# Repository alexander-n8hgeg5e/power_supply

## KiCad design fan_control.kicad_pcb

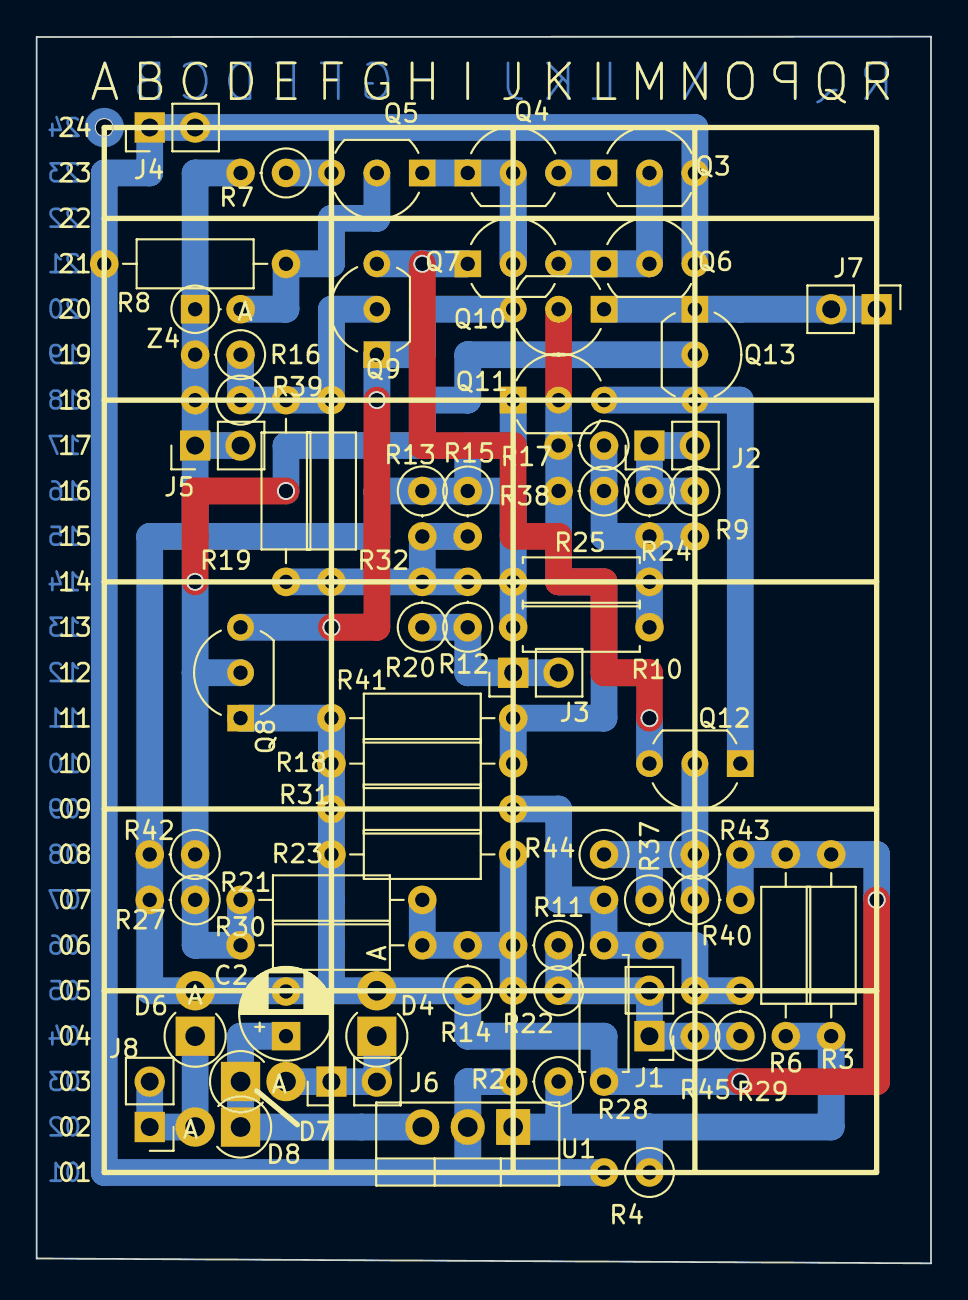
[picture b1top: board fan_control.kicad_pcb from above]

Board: 2 copper layers, 50.0 x 68.6 mm, 64 parts (0 on the bottom side), 26 nets.

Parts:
C2: elko; CP_Radial_D5.0mm_P2.50mm
D4, D6, D7, D8: 1N4007; D_DO-41_SOD81_P2.54mm_Vertical_AnodeUp
J1, J2, J3, J4, J5, J6, J7, J8: Conn_01x02_Male; PinHeader_1x02_P2.54mm_Vertical
Q3, Q4, Q6, Q7, Q8, Q9, Q10, Q11, Q12, Q13: BC557; TO-92_Inline_Wide
Q5: BC547B; TO-92_Inline_Wide
R2, R4: R; R_Axial_DIN0207_L6.3mm_D2.5mm_P2.54mm_Vertical
R3, R6: R; R_Axial_DIN0207_L6.3mm_D2.5mm_P10.16mm_Horizontal
R7: 20k; R_Axial_DIN0207_L6.3mm_D2.5mm_P2.54mm_Vertical
R8: spice; R_Axial_DIN0207_L6.3mm_D2.5mm_P10.16mm_Horizontal
R9, R24: 300K; R_Axial_DIN0207_L6.3mm_D2.5mm_P2.54mm_Vertical
R10, R25: 100K; R_Axial_DIN0207_L6.3mm_D2.5mm_P7.62mm_Horizontal
R11, R22, R29, R45: 150K; R_Axial_DIN0207_L6.3mm_D2.5mm_P2.54mm_Vertical
R12, R20: 150k; R_Axial_DIN0207_L6.3mm_D2.5mm_P2.54mm_Vertical
R13, R15: 50k; R_Axial_DIN0207_L6.3mm_D2.5mm_P2.54mm_Vertical
R14: 50K; R_Axial_DIN0207_L6.3mm_D2.5mm_P2.54mm_Vertical
R16, R17, R27, R37, R38, R39, R40, R42, R43, R44: 100K; R_Axial_DIN0207_L6.3mm_D2.5mm_P2.54mm_Vertical
R18, R19, R21, R30, R32, R41: 100K; R_Axial_DIN0207_L6.3mm_D2.5mm_P10.16mm_Horizontal
R23, R31: 50K; R_Axial_DIN0207_L6.3mm_D2.5mm_P10.16mm_Horizontal
R28: 50K; R_Axial_DIN0207_L6.3mm_D2.5mm_P7.62mm_Horizontal
U1: LM317_3PinPackage; TO-220-3_Vertical
Z4: 5V; D_DO-35_SOD27_P2.54mm_Vertical_AnodeUp

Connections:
0: C2.2, D4.2, D6.2, J5.1, J5.2, Q8.1, Q11.1, R3.2, R6.2, R7.2, R10.1, R13.1, R14.1, R15.1, R16.2, R18.2, R23.1, R25.1, R27.2, R28.2, R31.2, R39.2, R40.2, R41.2, R42.2, R43.2, Z4.1
0VAC: D6.1, D8.2, J8.1, J8.2
+15V: J4.1, J4.2, Q3.3, Q6.3, R2.2, R4.2, R8.1, U1.2
+15VAC: D4.1, D7.2, J6.1, J6.2
B: J2.1, J2.2, R9.1, R24.1
C: J3.1, J3.2, R12.1, R20.1
E: J1.1, J1.2, R11.1, R22.1, R29.1, R45.1
F+: J7.1, J7.2, Q10.1, Q13.1
unnamed: C2.1, D7.1, D8.1, U1.3
unnamed: Q3.1, Q4.3
unnamed: Q3.2, Q6.1, Q6.2, Q7.3
unnamed: Q4.1, Q4.2, Q5.1, Q7.2
unnamed: Q5.2, R8.2, Z4.2
unnamed: Q5.3, R7.1
unnamed: Q8.3, Q9.1, Q10.3
unnamed: Q11.3, Q12.1, Q13.3
unnamed: Q7.1, Q9.3, Q12.3
unnamed: R2.1, R3.1, R4.1, R6.1, U1.1
unnamed: R9.2, R10.2, R17.1, R24.2, R25.2, R38.1
unnamed: R11.2, R14.2, R21.2, R22.2, R23.2, R30.2
unnamed: R12.2, R13.2, R15.2, R19.1, R20.2, R32.1
unnamed: R28.1, R29.2, R31.1, R37.2, R44.2, R45.2
bias_i: Q10.2, Q11.2, R17.2, R18.1, R38.2, R41.1
bias_l: Q9.2, R16.1, R19.2, R32.2, R39.1
bias_o: Q8.2, Q13.2, R21.1, R27.1, R30.1, R42.1
bias_r: Q12.2, R37.1, R40.1, R43.1, R44.1

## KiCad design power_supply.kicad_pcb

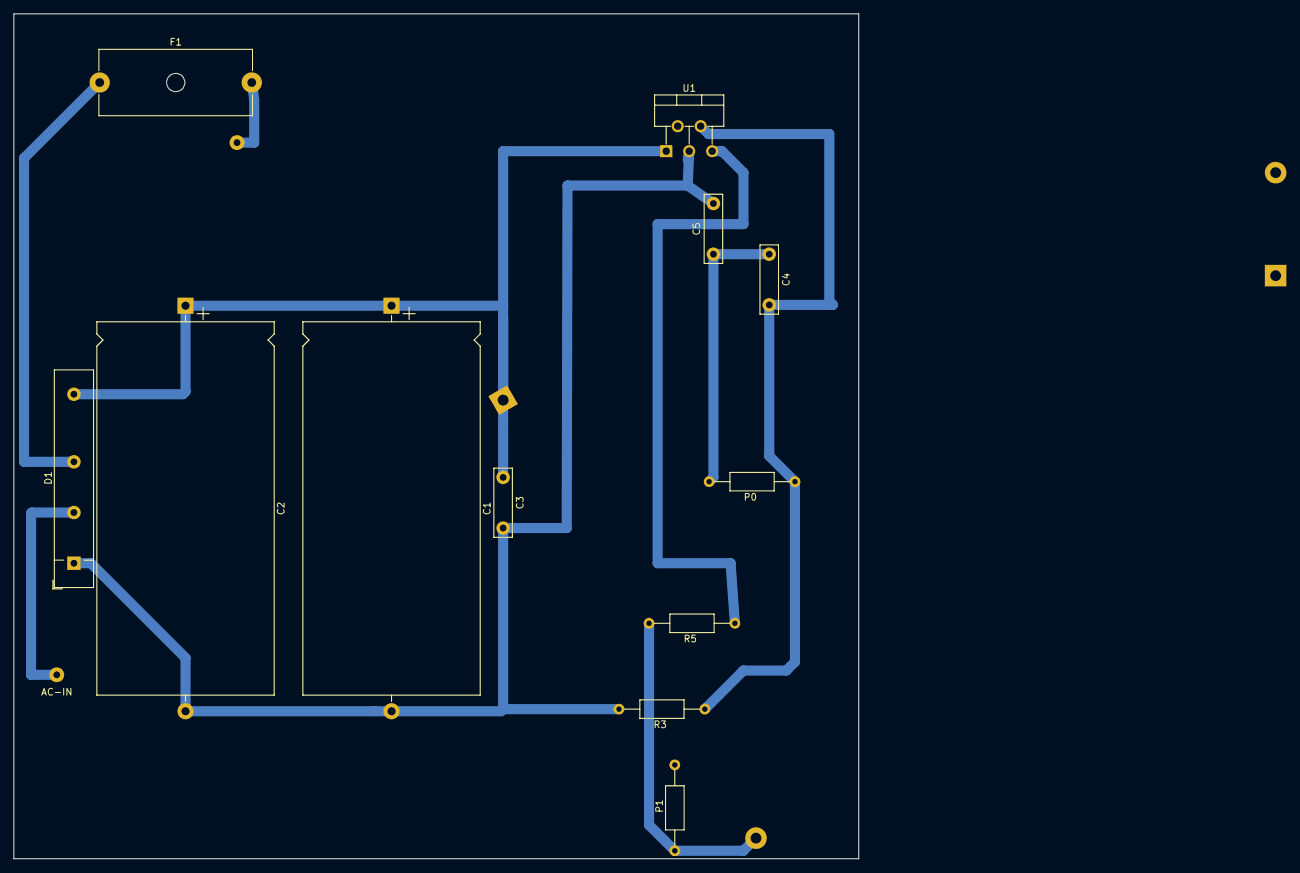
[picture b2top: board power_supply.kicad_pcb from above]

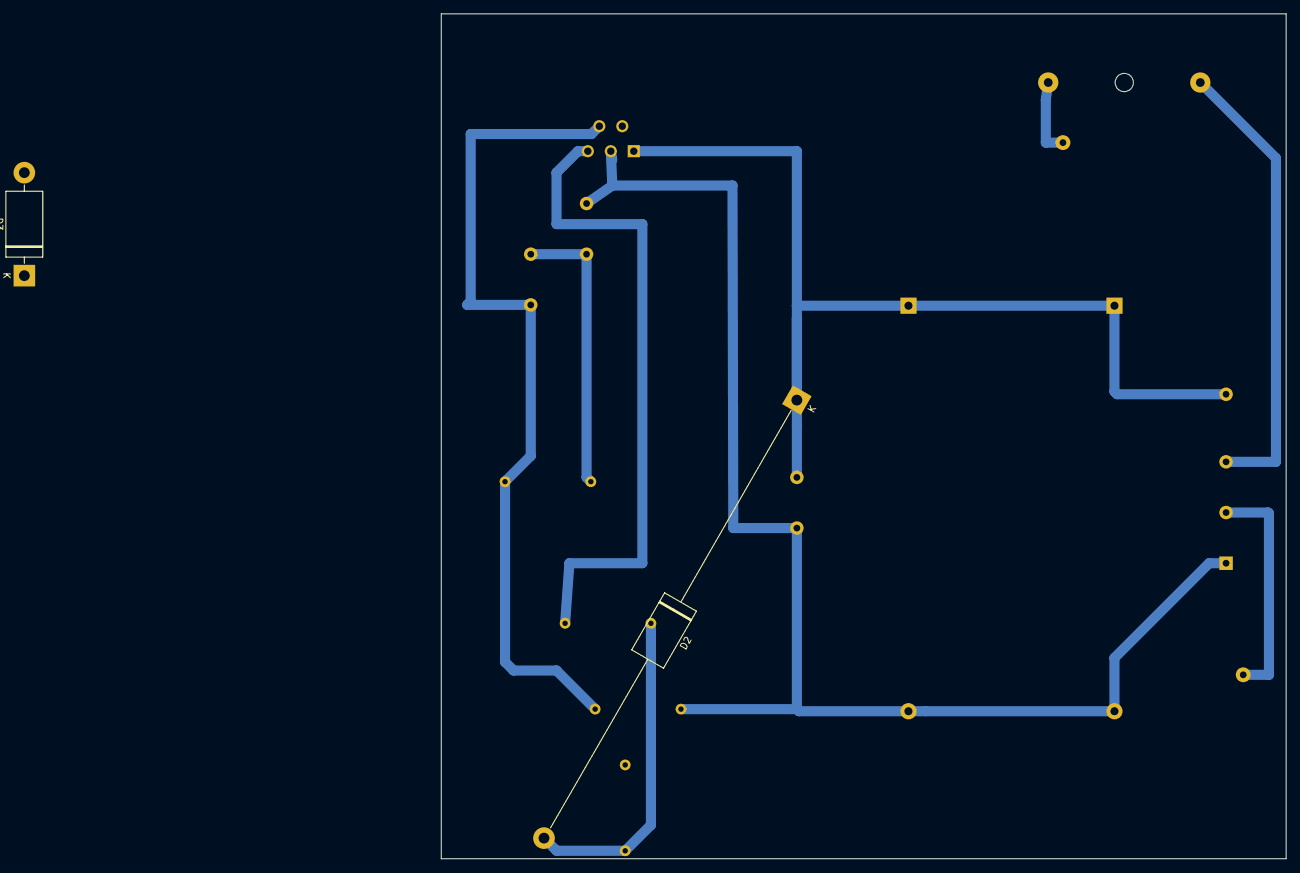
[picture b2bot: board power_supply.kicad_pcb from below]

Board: 2 copper layers, 125.0 x 125.0 mm, 14 parts (2 on the bottom side), 7 nets.

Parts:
C1: 4.7uF 63V; CP_Axial_L55.0mm_D26.0mm_P60.00mm_Horizontal
C2: 4.7mF 63V; CP_Axial_L55.0mm_D26.0mm_P60.00mm_Horizontal
C3, C4, C5: 0.1uF 100V; C_Rect_L10.0mm_W2.5mm_P7.50mm_MKS4
D1: B80C3700-2200A; Diode_Bridge_32.0x5.6x17.0mm_P10.0mm_P7.5mm
D2: 1N5408; D_DO-201AD_P75.21mm_Horizontal_extra_long
D3: 1N5408; D_DO-201AD_P15.24mm_Horizontal
F1: Fuse; Fuseholder_Cylinder-5x20mm_Schurter_0031_8201_Horizontal_Op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
P0: 10K; R_Axial_DIN0207_L6.3mm_D2.5mm_P12.7mm_Horizontal
P1: 100; R_Axial_DIN0207_L6.3mm_D2.5mm_P12.7mm_Horizontal
R3, R5: R; R_Axial_DIN0207_L6.3mm_D2.5mm_P12.7mm_Horizontal
U1: L200; TO-220-5_P3.4x3.7mm_StaggerOdd_Lead3.8mm_Vertical

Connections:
B: R5.1, U1.5
C: C1.1, C2.1, C3.1, D1.4, D2.1, U1.1
E: D2.2, P1.1, R5.2
GND: C1.2, C2.2, C3.2, C5.2, D1.1, D3.2, R3.2, U1.3
unnamed: C4.1, C5.1, D3.1, P0.2
unnamed: C4.2, P0.1, R3.1, U1.4
unnamed: D1.3, F1.1

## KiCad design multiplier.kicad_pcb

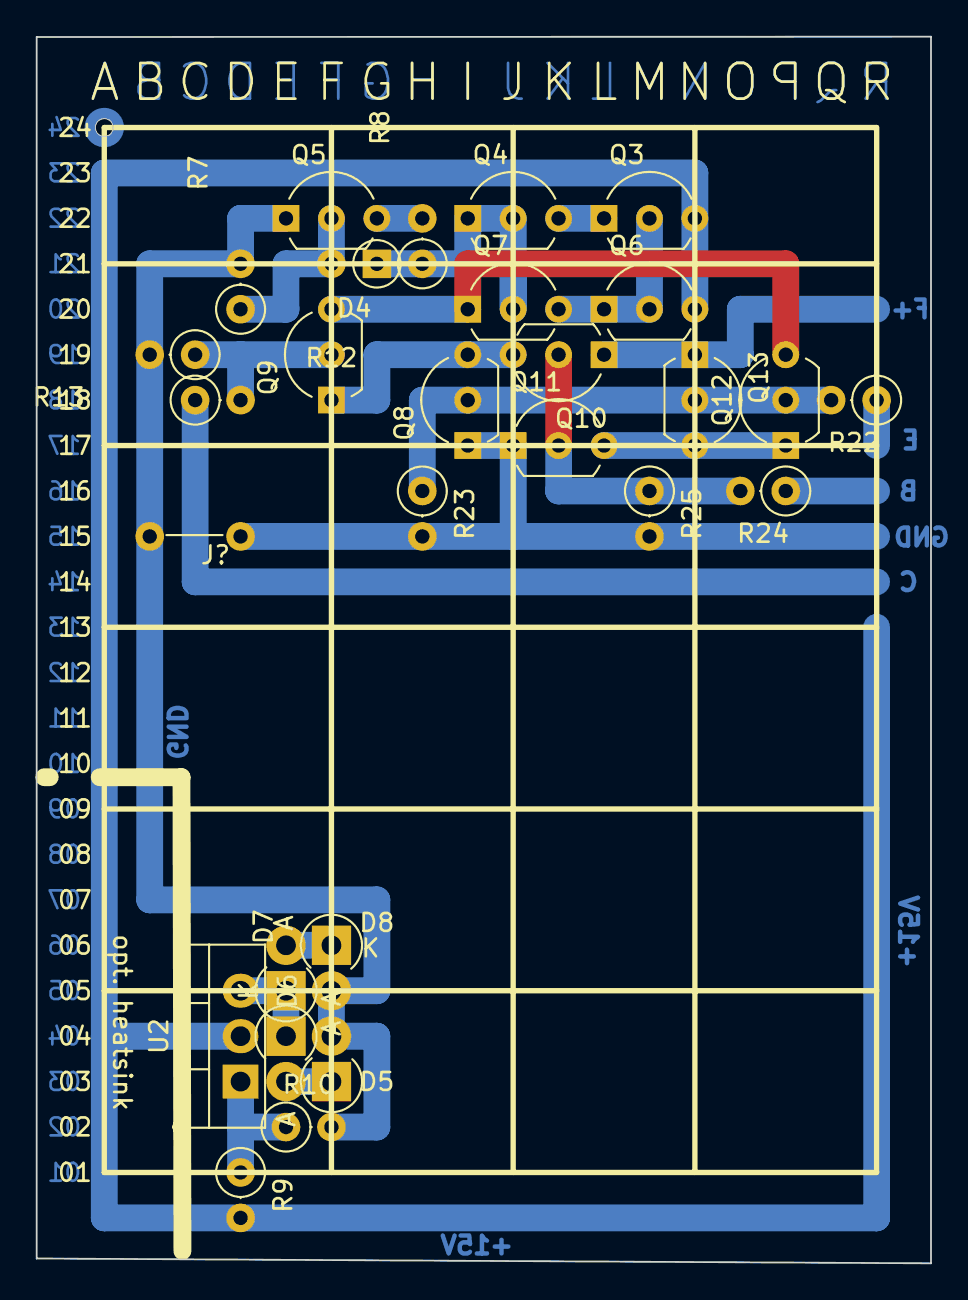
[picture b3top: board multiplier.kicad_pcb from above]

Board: 2 copper layers, 50.0 x 68.6 mm, 28 parts (0 on the bottom side), 18 nets.

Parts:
D4: D_Zener; D_DO-35_SOD27_P2.54mm_Vertical_AnodeUp
D5, D6, D7, D8: 1N4007; D_DO-41_SOD81_P2.54mm_Vertical_AnodeUp
J?: wire bridge; wire_bridge_5.08
Q3, Q4, Q5, Q6, Q7, Q8, Q9, Q10, Q11, Q13: BC557; TO-92L_Inline_Wide
Q12: BC557; TO-92_Inline_Wide
R7, R8: 10K; R_Axial_DIN0207_L6.3mm_D2.5mm_P2.54mm_Vertical
R9, R10: R; R_Axial_DIN0207_L6.3mm_D2.5mm_P2.54mm_Vertical
R12, R22, R24: 150K; R_Axial_DIN0207_L6.3mm_D2.5mm_P2.54mm_Vertical
R13, R23, R25: 50K; R_Axial_DIN0207_L6.3mm_D2.5mm_P2.54mm_Vertical
U2: LM317_3PinPackage; TO-220-3_Vertical

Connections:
/fan_control/+15V: Q3.3, Q6.3, R9.2, U2.2
/fan_control/GND: D6.2, D8.2, J?.1, J?.2, Q5.1, Q8.1, Q11.1, R7.2, R10.2, R13.2, R23.2, R25.2
/fan_control/multiplier/F+: Q10.1, Q13.1
unnamed: D4.1, Q4.1, Q4.2, Q7.2, R8.1
unnamed: D4.2, Q5.2, R7.1
unnamed: D5.1, D7.1, U2.3
unnamed: D5.2, D6.1
unnamed: D7.2, D8.1
unnamed: Q3.1, Q4.3
unnamed: Q3.2, Q6.1, Q6.2, Q7.3
unnamed: Q5.3, R8.2
unnamed: Q9.2, R12.2, R13.1
unnamed: Q10.2, Q11.2, R24.2, R25.1
unnamed: Q8.3, Q9.1, Q10.3
unnamed: Q11.3, Q12.1, Q13.3
unnamed: Q8.2, Q12.2, Q13.2, R22.2, R23.1
unnamed: Q7.1, Q9.3, Q12.3
unnamed: R9.1, R10.1, U2.1

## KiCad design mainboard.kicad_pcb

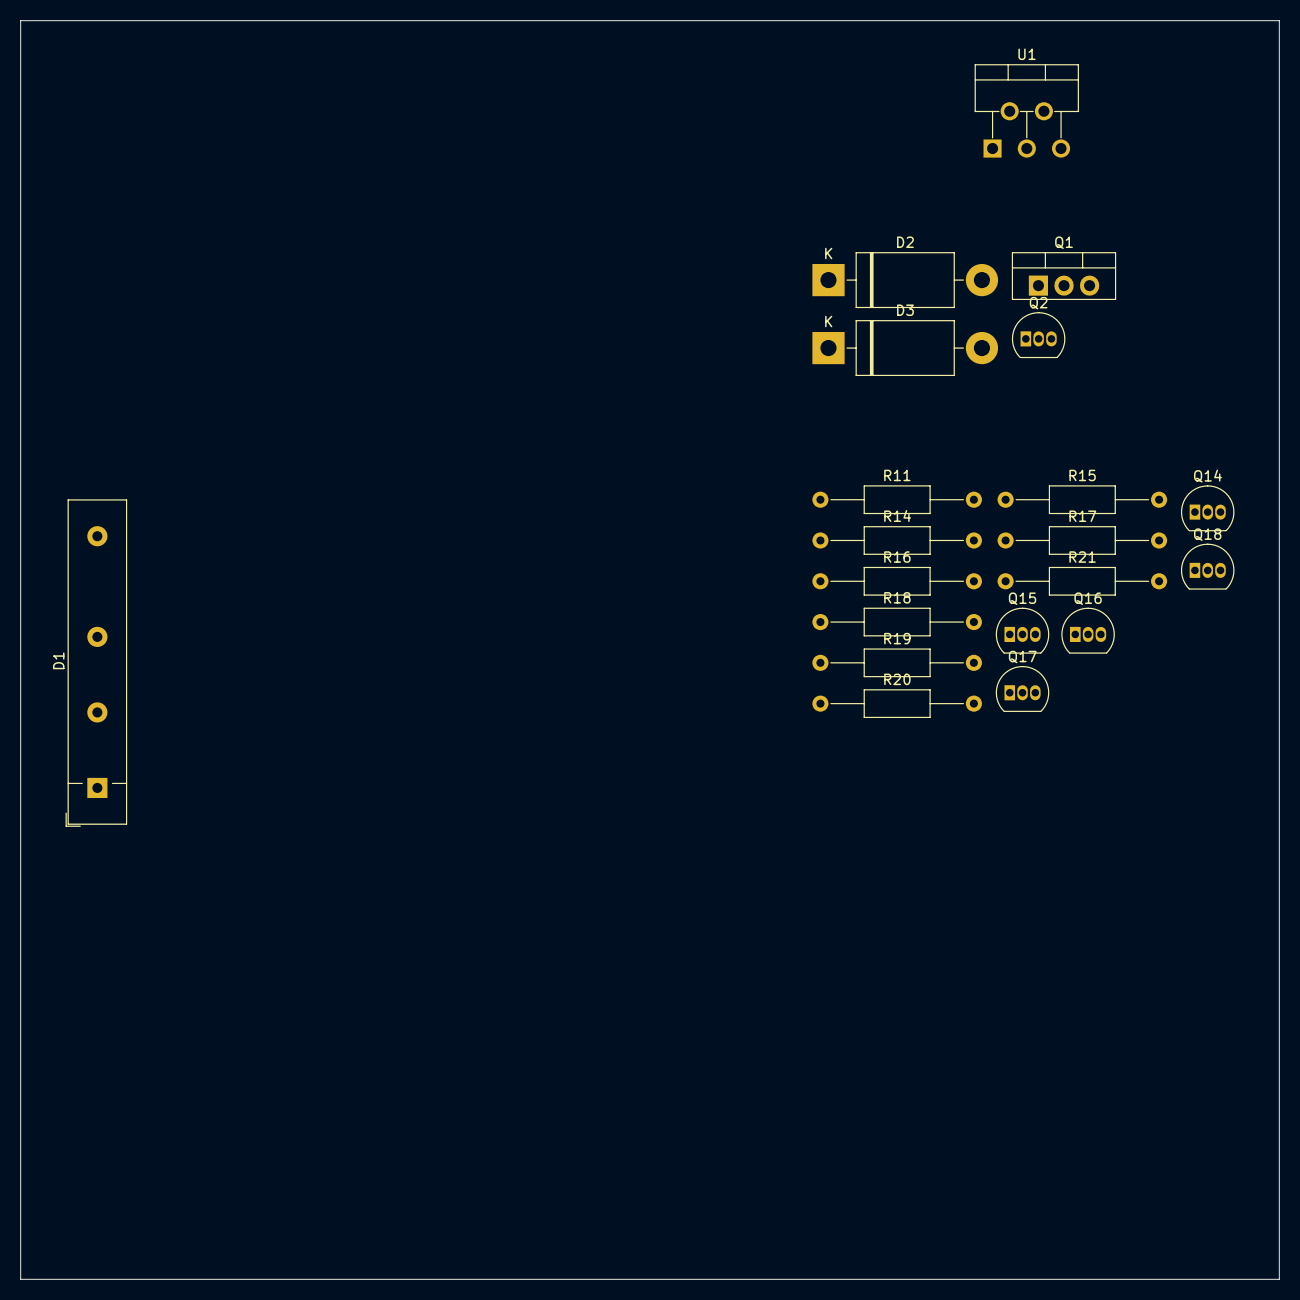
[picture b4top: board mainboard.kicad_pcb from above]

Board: 2 copper layers, 125.0 x 125.0 mm, 20 parts (0 on the bottom side), 18 nets, no tracks yet.

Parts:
D1: B80C3700-2200A; Diode_Bridge_32.0x5.6x17.0mm_P10.0mm_P7.5mm
D2, D3: 1N5408; D_DO-201AD_P15.24mm_Horizontal
Q1: BUT11A; TO-220-3_Vertical
Q2, Q14, Q15, Q16, Q17, Q18: BC547; TO-92_Inline
R11, R15, R17, R19, R21: 10K; R_Axial_DIN0207_L6.3mm_D2.5mm_P15.24mm_Horizontal
R14, R16, R18, R20: 22; R_Axial_DIN0207_L6.3mm_D2.5mm_P15.24mm_Horizontal
U1: L200; TO-220-5_P3.4x3.7mm_StaggerOdd_Lead3.8mm_Vertical

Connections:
/fan_control/+15V: Q14.1, Q15.1, Q16.1, Q17.1, Q18.1
/fan_control/multiplier/F-: Q14.3, R11.2, R15.2, R17.2, R19.2
B: Q1.1, U1.5
C: D1.4, D2.1, Q1.2, U1.1
E: D2.2, Q1.3
GND: D1.1, D3.2, U1.3
unnamed: D3.1, Q2.3
unnamed: R14.1, R16.1, R18.1, R20.1
unnamed: Q2.1, U1.2
unnamed: Q14.2, R21.1
unnamed: Q15.2, R11.1
unnamed: Q15.3, R14.2
unnamed: Q16.2, R15.1
unnamed: Q16.3, R16.2
unnamed: Q17.2, R17.1
unnamed: Q17.3, R18.2
unnamed: Q18.2, R19.1
unnamed: Q18.3, R20.2

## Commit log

2020-04-02 init
2020-06-30 progress on schematics
2020-06-30 footprint assoziation; pcb layout; and more
    * delete mainboard pcb
    * rearrange project files/names
    * create pcb layout
    * improve schematics
    * more
2020-06-30 gen bom; add python tool
2020-06-30 add adjustment resistors
2020-06-30 add silkscreen references
    ...
2020-06-30 add resistors
    ...
2020-06-30 update bom
2020-06-30 move silkscreen lines to correct spot
2020-06-30 mv label
2020-06-30 make res references more readable; assign references to combined values
2020-06-30 add lm317 Vout calc text
2020-06-30 search and combine resistors
2020-06-30 add resistors to pcb
2020-06-30 add license stuff
